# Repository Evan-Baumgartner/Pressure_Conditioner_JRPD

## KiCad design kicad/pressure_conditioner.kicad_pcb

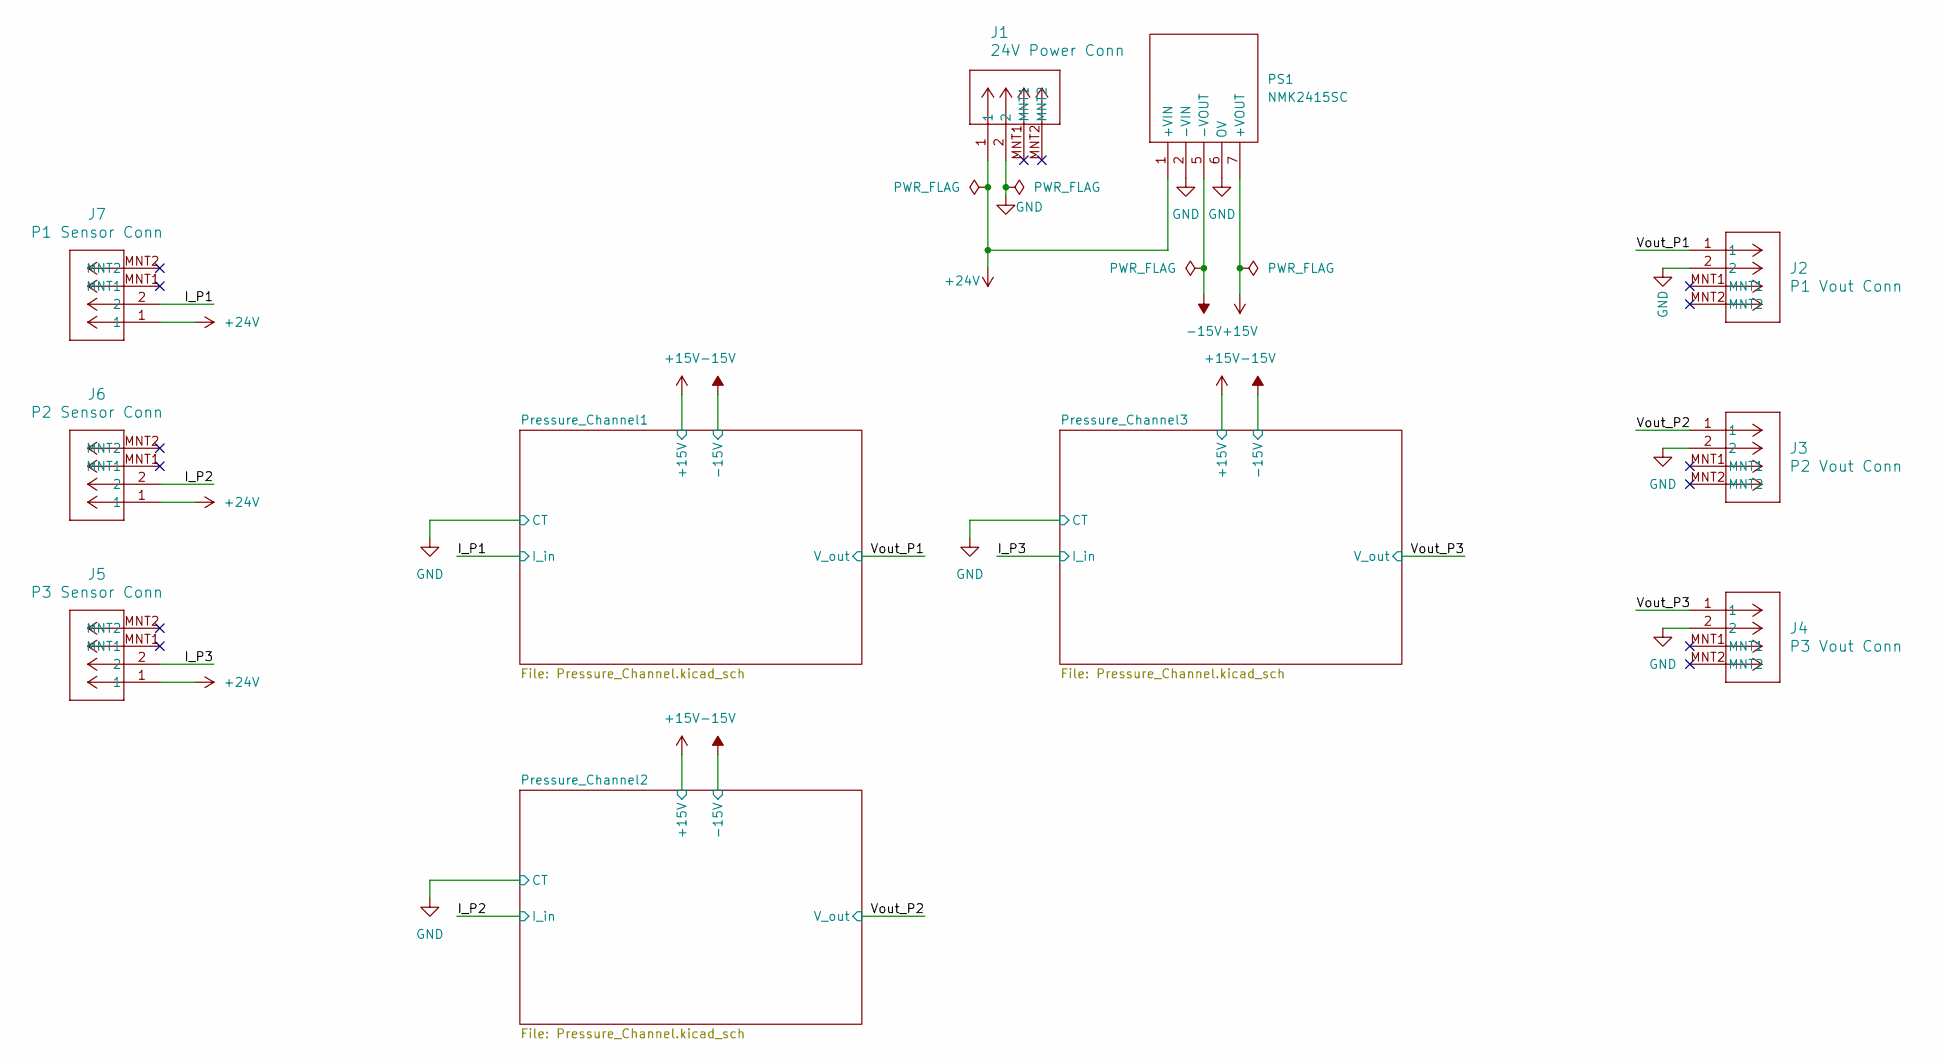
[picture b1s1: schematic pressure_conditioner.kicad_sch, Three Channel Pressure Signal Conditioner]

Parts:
J1: 24V Power Conn; MOLEX_5023520201_2_Wire_DuraClik
J2: P1 Vout Conn; MOLEX_5023520201_2_Wire_DuraClik
J3: P2 Vout Conn; MOLEX_5023520201_2_Wire_DuraClik
J4: P3 Vout Conn; MOLEX_5023520201_2_Wire_DuraClik
J5: P3 Sensor Conn; MOLEX_5023520201_2_Wire_DuraClik
J6: P2 Sensor Conn; MOLEX_5023520201_2_Wire_DuraClik
J7: P1 Sensor Conn; MOLEX_5023520201_2_Wire_DuraClik
PS1: NMK2415SC; Murata_24-+-15_Conv_NMK2415SC; Manufacturer_Part_Number NMK2415SC; Mouser Part Number 580-NMK2415SC

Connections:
+15V: PS1.7 (+VOUT); also elsewhere on the board
+24V: J1.1, J5.1, J6.1, J7.1, PS1.1 (+VIN)
-15V: PS1.5 (-VOUT); also elsewhere on the board
/I_P1: J7.2; also elsewhere on the board
/I_P2: J6.2; also elsewhere on the board
/I_P3: J5.2; also elsewhere on the board
/Vout_P1: J2.1; also elsewhere on the board
/Vout_P2: J3.1; also elsewhere on the board
/Vout_P3: J4.1; also elsewhere on the board
GND: J1.2, J2.2, J3.2, J4.2, PS1.2 (-VIN), PS1.6 (OV); also elsewhere on the board

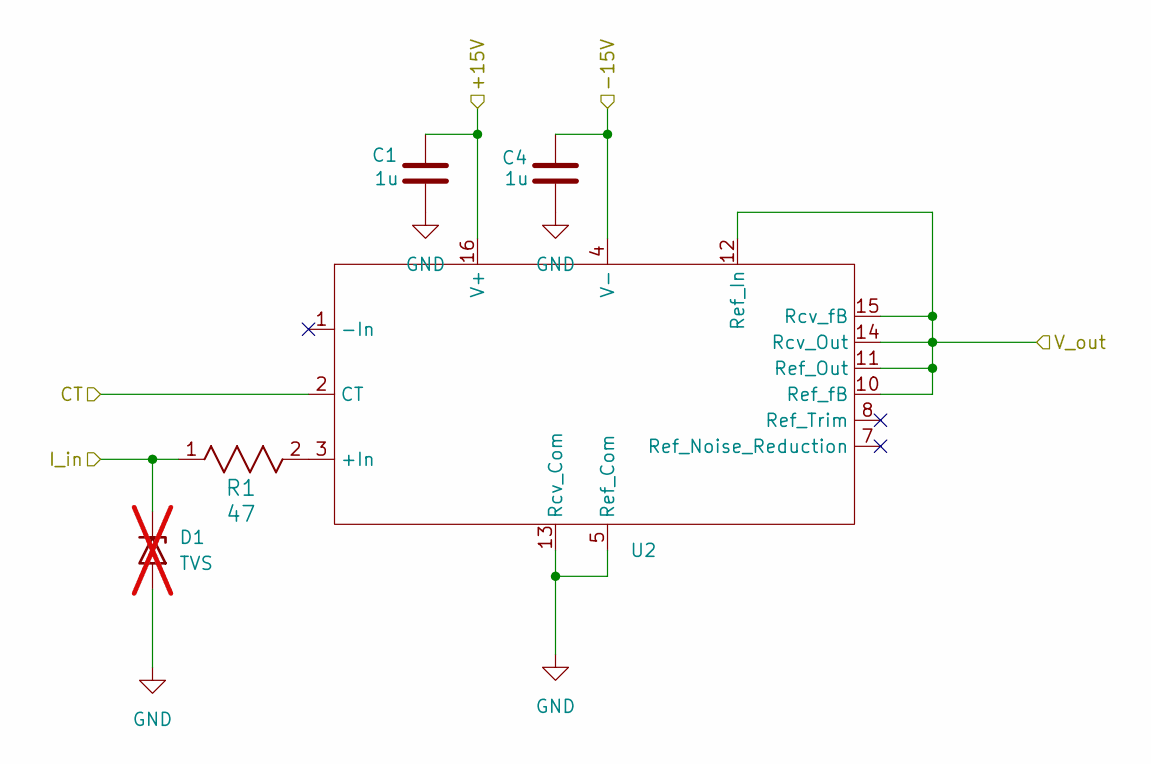
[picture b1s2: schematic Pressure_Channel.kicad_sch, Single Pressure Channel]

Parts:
C1, C4: 1u; C_0805_2012Metric_Pad1.18x1.45mm_HandSolder
D1: TVS; D_SMB; not fitted
R1: 47; R_2512_6332Metric_Pad1.40x3.35mm_HandSolder
U2: CERDIP-16_W7.62mm_SideBrazed

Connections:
+15V: C1.1, U2.16 (V+); also elsewhere on the board
-15V: C4.1, U2.4 (V-); also elsewhere on the board
/I_P1: D1.1 (A1), R1.1; also elsewhere on the board
/Vout_P1: U2.10 (Ref_fB), U2.11 (Ref_Out), U2.12 (Ref_In), U2.14 (Rcv_Out), U2.15 (Rcv_fB); also elsewhere on the board
GND: C1.2, C4.2, D1.2 (A2), U2.2 (CT), U2.5 (Ref_Com), U2.13 (Rcv_Com); also elsewhere on the board
unnamed: R1.2, U2.3 (+In)

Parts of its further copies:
C2, C3, C5, C6: 1u; C_0805_2012Metric_Pad1.18x1.45mm_HandSolder
D2, D3: TVS; D_SMB; not fitted
R2, R3: 47; R_2512_6332Metric_Pad1.40x3.35mm_HandSolder

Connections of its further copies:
+15V: C2.1, C3.1; also elsewhere on the board
-15V: C5.1, C6.1; also elsewhere on the board
/I_P2: D2.1 (A1), R2.1; also elsewhere on the board
/I_P3: D3.1 (A1), R3.1; also elsewhere on the board
GND: C2.2, C3.2, C5.2, C6.2, D2.2 (A2), D3.2 (A2); also elsewhere on the board
unnamed 11: R2.2; also elsewhere on the board
unnamed 12: R3.2; also elsewhere on the board

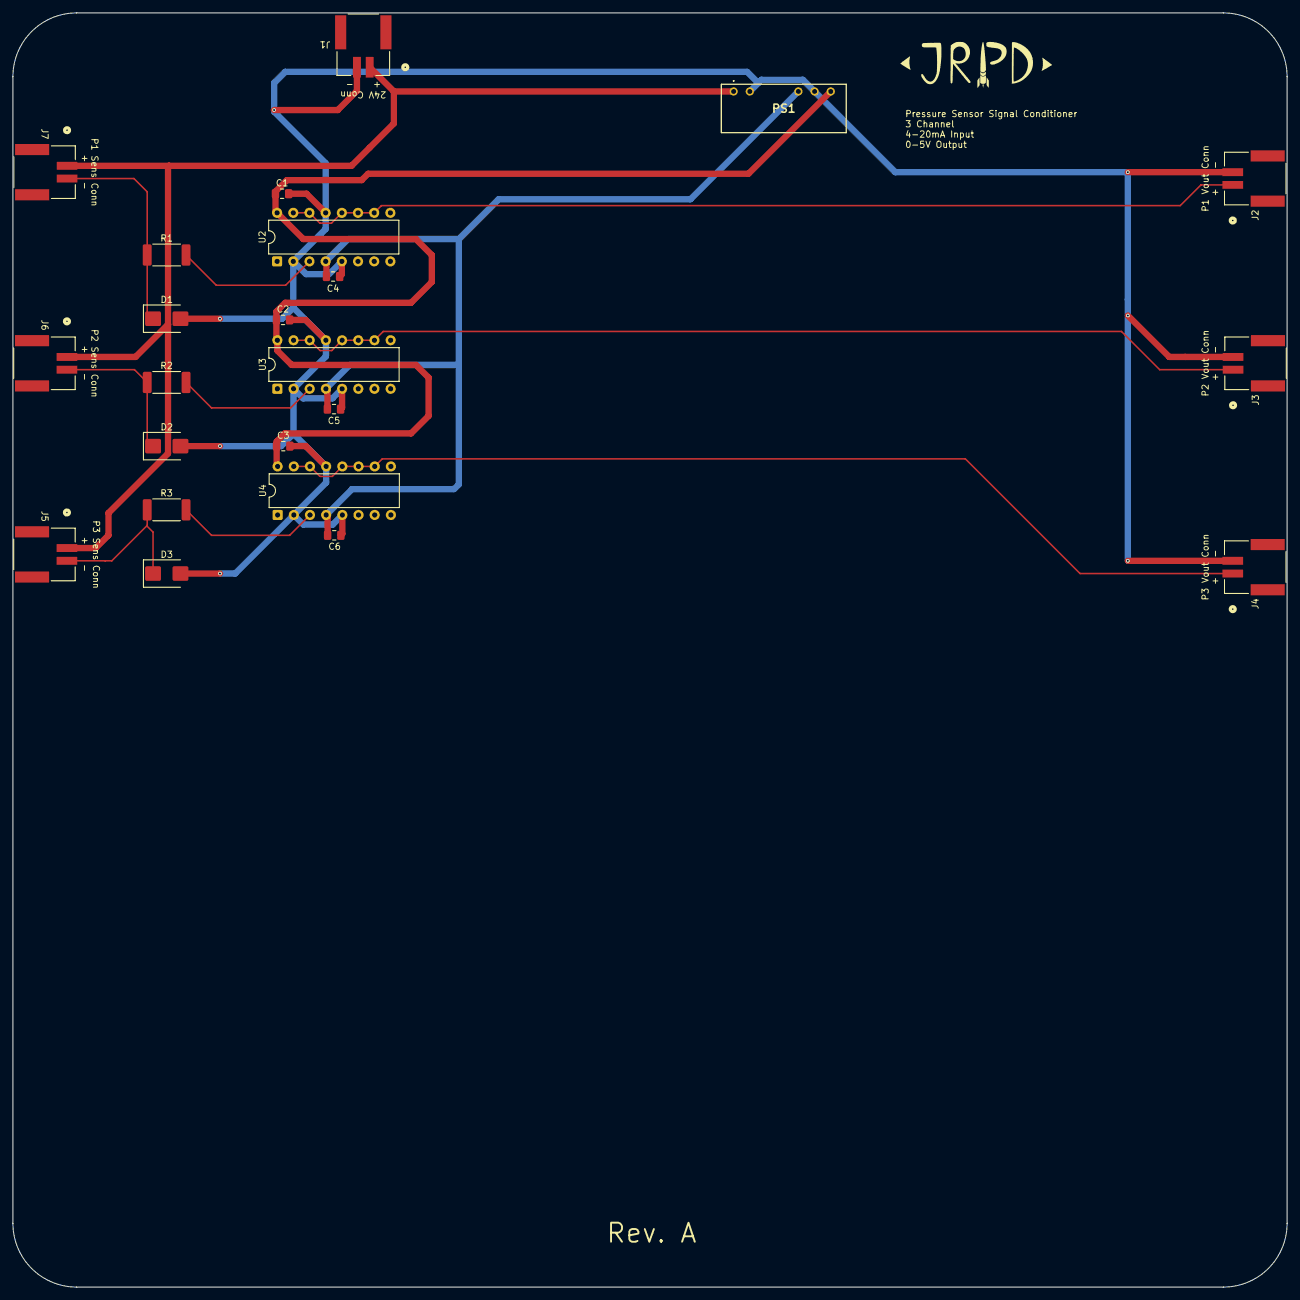
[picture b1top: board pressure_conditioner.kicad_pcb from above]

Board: 2 copper layers, 200.0 x 200.0 mm, 23 parts (0 on the bottom side), 13 nets.

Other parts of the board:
U3, U4: CERDIP-16_W7.62mm_SideBrazed

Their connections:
+15V: U3.16 (V+), U4.16 (V+); also elsewhere on the board
-15V: U3.4 (V-), U4.4 (V-); also elsewhere on the board
/Vout_P2: U3.10 (Ref_fB), U3.11 (Ref_Out), U3.12 (Ref_In), U3.14 (Rcv_Out), U3.15 (Rcv_fB); also elsewhere on the board
/Vout_P3: U4.10 (Ref_fB), U4.11 (Ref_Out), U4.12 (Ref_In), U4.14 (Rcv_Out), U4.15 (Rcv_fB); also elsewhere on the board
GND: U3.2 (CT), U3.5 (Ref_Com), U3.13 (Rcv_Com), U4.2 (CT), U4.5 (Ref_Com), U4.13 (Rcv_Com); also elsewhere on the board
unnamed 11: U3.3 (+In); also elsewhere on the board
unnamed 12: U4.3 (+In); also elsewhere on the board
